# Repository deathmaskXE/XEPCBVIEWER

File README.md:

# XE Delivery

Aplicación web para repartidores independientes: mandados, compras, mensajería, seguimiento público, reputación y rendimiento. Es una sola aplicación multi-repartidor; toda información privada se separa mediante `courierId`, igual al UID de Firebase Authentication.

## Tecnologías

React, Vite, React Router con `HashRouter`, Firebase Authentication y Firestore modular, Chart.js, jsPDF, html2canvas, Leaflet/OpenStreetMap y Lucide. No utiliza Storage, Analytics, Realtime Database, cartera, saldo ni retiros.

## Instalación y ejecución

1. Instala Node.js 20 o superior.
2. Ejecuta `npm install`.
3. Copia `.env.example` como `.env` y completa únicamente las variables públicas de configuración web de Firebase.
4. Ejecuta `npm run dev`.
5. Para validar producción: `npm run build` y `npm run preview`.

La auditoría final del 18 de julio de 2026 confirmó una instalación reproducible y una compilación de producción correcta. El proyecto usa carga diferida por página y `HashRouter`, por lo que no necesita reescrituras de rutas en GitHub Pages.

Si no hay configuración Firebase, la interfaz entra en modo demostración con datos ficticios. También puede activarse de forma explícita con `VITE_DEMO_MODE=true`. Nunca debe activarse en producción.

## Preparar Firebase

1. En un proyecto Firebase existente, activa Authentication por correo/contraseña y Cloud Firestore en modo producción. No actives Analytics ni Storage.
2. Registra una aplicación web y copia sus valores a `.env`; estas claves identifican la app y no sustituyen las reglas de seguridad.
3. Publica reglas e índices con Firebase CLI: `firebase deploy --only firestore`.
4. Crea manualmente el primer usuario administrador en Authentication, copia su UID y crea `users/{uid}` con `uid`, `role: "admin"`, `status: "approved"`, `displayName`, `email`, `phone`, `createdAt` y `updatedAt`. No guardes contraseñas en Firestore.
5. Conserva la cuenta administrativa con autenticación multifactor y acceso restringido a la consola.

## Colecciones

`users`, `couriers`, `courierAccessRoutes`, `licenses`, `clients`, `orders`, `orders/{id}/history`, `ratings`, `complaints`, `auditLogs` y `publicTracking`. Las consultas privadas siempre deben incluir `where('courierId','==',auth.currentUser.uid)`; las reglas vuelven a comprobar la propiedad. `publicTracking` contiene solo una proyección mínima y nunca notas, ganancias, correo, credencial o auditoría.

## Licencias y rutas privadas

La prueba normal usa `type: trial`, `status: trial` y `expiresAt` a 24 horas. La licencia de seis meses usa `type: six_months` y `status: active`. El contador lee el timestamp persistido y nunca lo reinicia localmente. Renovar o cambiar fechas es una operación administrativa auditada.

Una ruta se guarda en `courierAccessRoutes/{token}`. Al regenerarla, una Cloud Function/transacción administrativa debe desactivar la anterior y crear un token criptográficamente aleatorio. La ruta no reemplaza el login: después de autenticar, el UID debe coincidir con `courierId`. No coloque datos sensibles en el token o URL.

## Seguimiento público y confirmación de una hora

El navegador público solo lee `publicTracking/{trackingToken}`. La colección privada `orders` no está abierta al público. Una Cloud Function debe copiar únicamente campos permitidos cada vez que cambia un pedido.

Al entregar, el backend establece `waiting_client_confirmation`, `deliveredAt` y `autoConfirmAt = deliveredAt + 1 hora`. Una función programada completa pedidos vencidos. Una reconciliación en el cliente puede mejorar la experiencia, pero no garantiza ejecución cuando ninguna página está abierta y no debe tener permisos para confirmar arbitrariamente.

## Funciones backend recomendadas (plan Blaze)

- `syncPublicTracking`: proyección segura de pedidos a `publicTracking`.
- `submitPublicConfirmation`, `submitRating` y `submitComplaint`: endpoints con App Check, token de pedido, validación y protección de abuso.
- `autoConfirmDeliveredOrders`: tarea programada para la hora límite.
- `rotateCourierAccessRoute`: invalida la ruta anterior, crea la nueva y audita atómicamente.
- `adminUpdateOrder`, `archiveOrder` y operaciones de licencia: verifican custom claims/rol y registran auditoría.
- Agregados confiables de reputación, estadísticas y consecutivos por repartidor.

Cloud Functions y tareas programadas normalmente requieren el plan Blaze. Los límites y precios deben comprobarse en la documentación vigente de Firebase antes de activarlo.

## GitHub Pages

1. Para este repositorio usa `VITE_BASE_PATH=/XEDELIVERY/` en el entorno de compilación.
2. Ejecuta `npm run build`.
3. Publica con `npm run deploy`; el script usa `gh-pages -d dist`.
4. En GitHub, selecciona la rama `gh-pages` como origen de Pages.

`HashRouter` mantiene estables rutas como `#/acceso/{token}`, `#/seguimiento/{token}`, `#/courier/dashboard` y `#/admin/dashboard` al publicar en una subruta.

## Prueba manual sugerida

Usa `#/seguimiento/demo-128` en modo demo. En Firebase real, crea primero el pedido privado y deja que `syncPublicTracking` produzca su vista pública. Prueba con dos cuentas courier y confirma que cada consulta incluye su UID, y que las reglas rechazan lecturas cruzadas desde el emulador.

Consulta `IMPLEMENTATION_STATUS.md` antes de producción: enumera con precisión lo terminado y lo que necesita backend.

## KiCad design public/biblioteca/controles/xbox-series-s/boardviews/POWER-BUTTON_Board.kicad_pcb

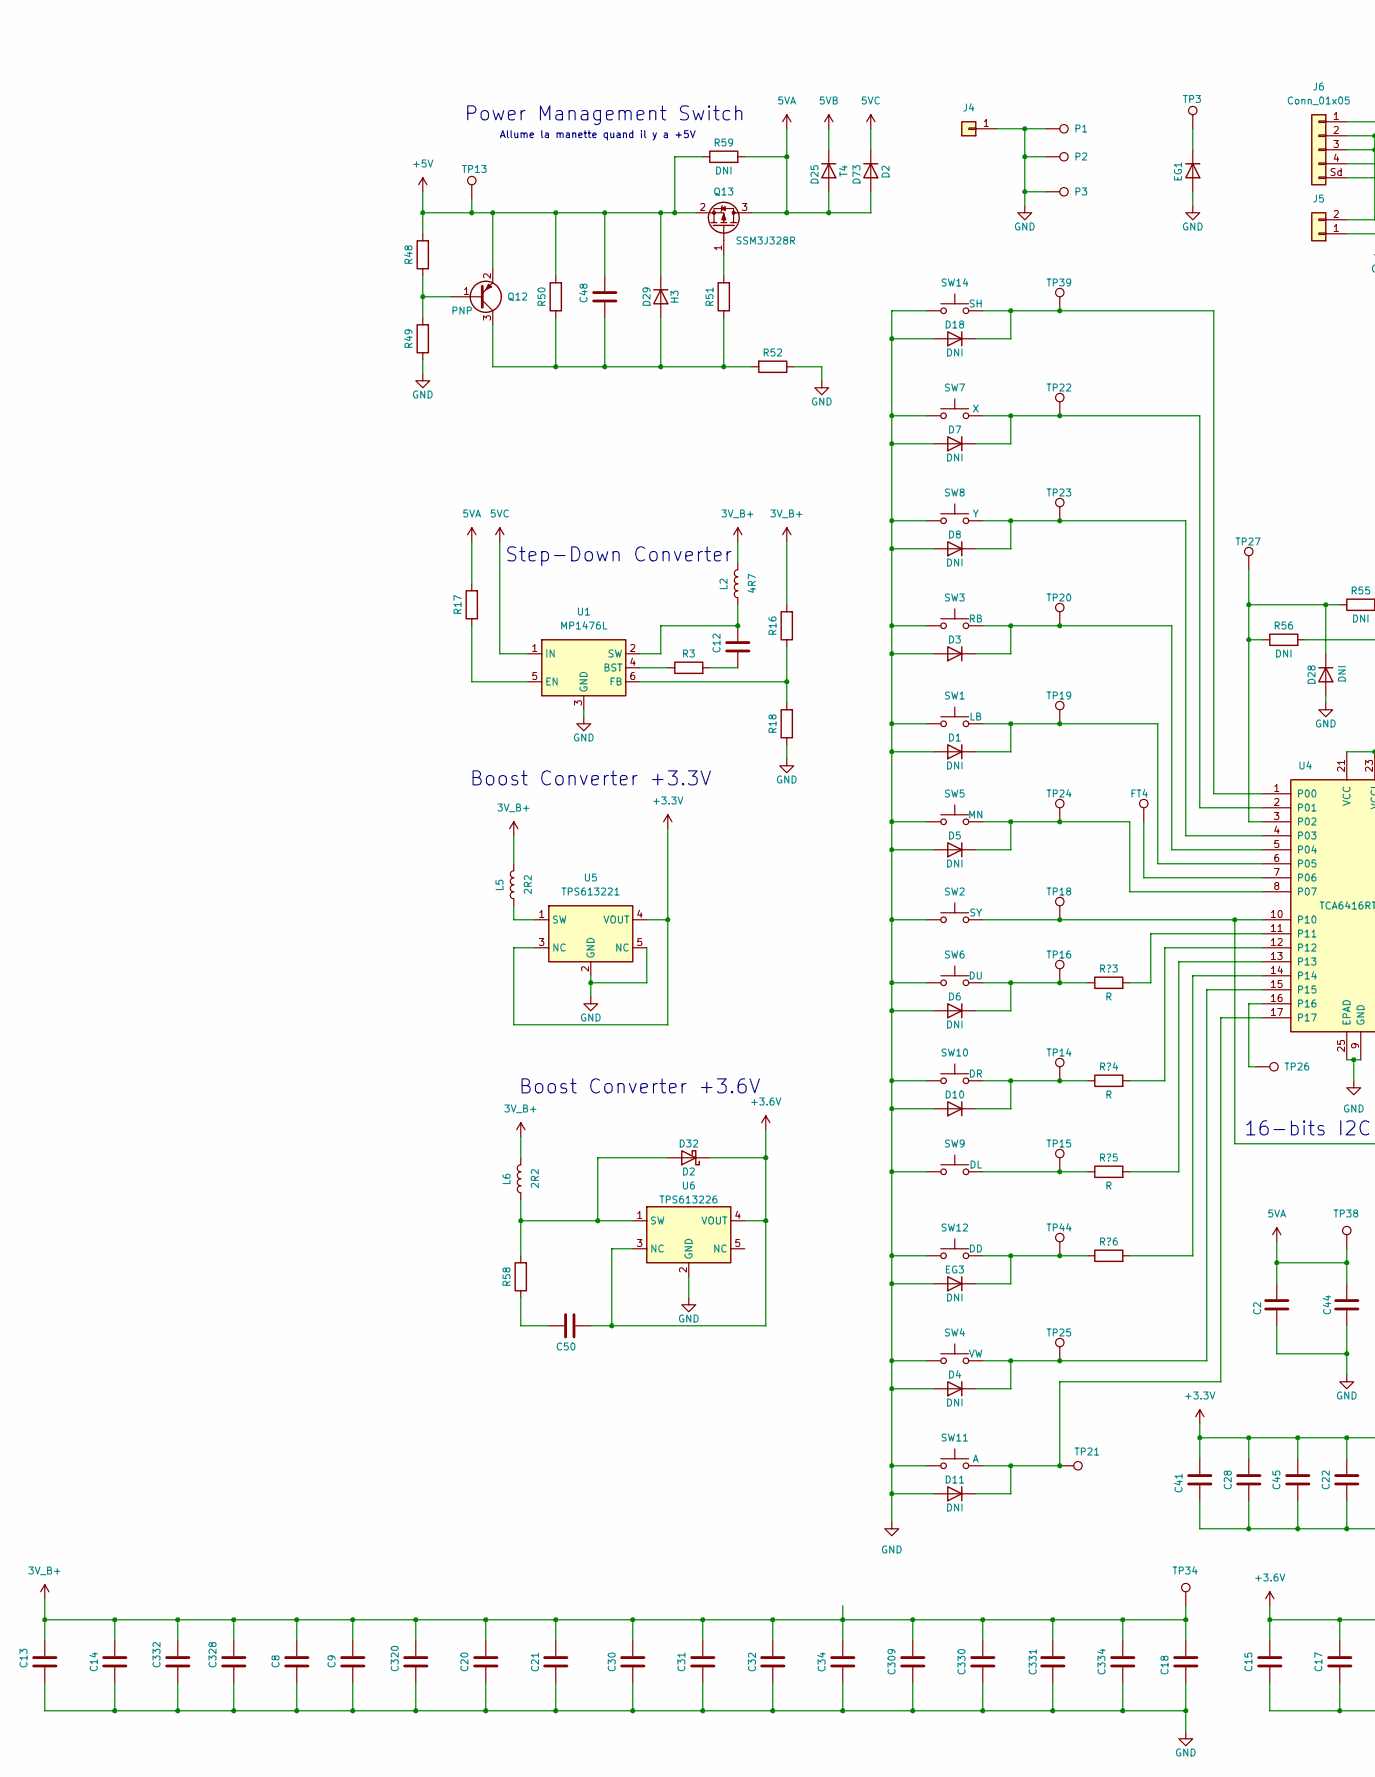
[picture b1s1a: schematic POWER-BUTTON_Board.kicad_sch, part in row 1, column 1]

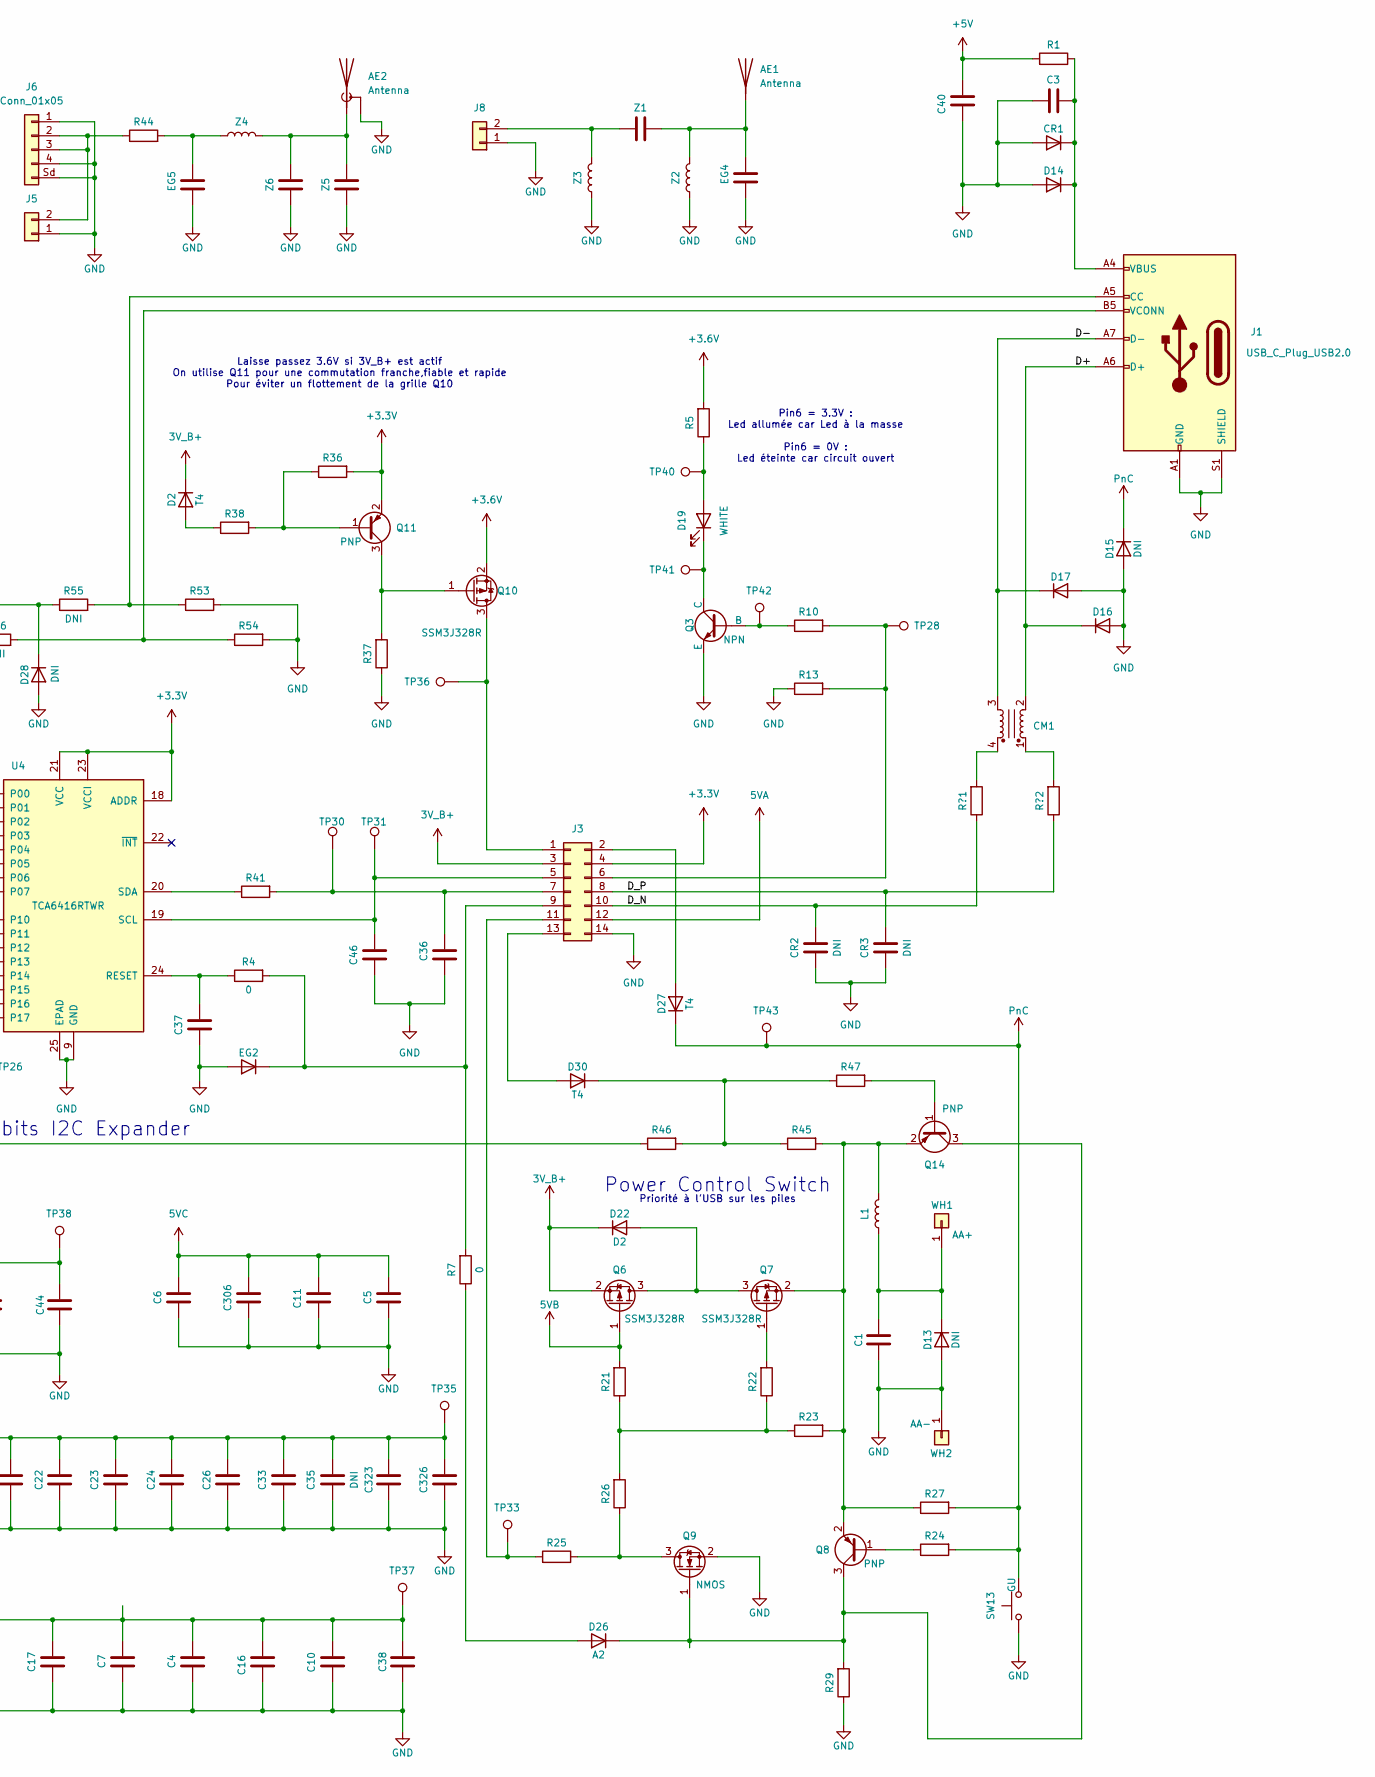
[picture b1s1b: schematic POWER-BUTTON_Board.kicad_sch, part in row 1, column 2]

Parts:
AE1: Antenna; Xbox_RFAntenna2
AE2: Antenna; Xbox_RFAntenna
C1, C12, C14, C15, C28, C36, C37, C45, C46, C48, C50: C; Xbox_C_01005_0402Metric
C2, C4, C8, C9, C13, C16, C20, C23, C26, C30, C31, C32, C34, C306: C; C_0402_1005Metric
C3, C5, C7, C10, C11, C17, C18, C24, C40, C44, C309, C320, C323, C326, C328, C330, C331, C332, C334: C; C_0201_0603Metric
C6: C; C_0504_1310Metric
C21, C22, C41: C; C_01005_0402Metric
C33: C; C_1206_3216Metric
C35: DNI; C_0603_1608Metric
C38: C; C_0603_1608Metric
CM1: Choke_Coilcraft_0603USB-142; L_CommonModeChoke_Coilcraft_0603USB
CR1: D; Xbox_Diode
CR2, CR3: DNI; D_0201_0603Metric
D1, D4, D5, D6, D7, D8, D11, D18: DNI; D_0201_0603Metric
D2, D25, D27, D30: T4; Xbox_Diode
D3, D10: D; D_0201_0603Metric
D13: DNI; R_01005_0402Metric
D14, D16, D17: D; D_01005_0402Metric
D15, D28: DNI; D_01005_0402Metric
D19: WHITE; LED_0805_2012Metric
D22, D32, D73: D2; Xbox_Diode
D26: A2; Xbox_Diode
D29: H3; Xbox_Diode
EG1: D; Xbox_R_01005_0402Metric
EG2: D; D_0201_0603Metric
EG3: DNI; Xbox_R_01005_0402Metric
EG4, EG5: C; C_0402_1005Metric
FT4: TestPoint; Xbox_TestPoint_0.8mm
J1: USB_C_Plug_USB2.0; Xbox_USB_C
J3: Conn_02x07; PinSocket_2x07_P1.27mm_Vertical_SMD
J4: Conn_01x01; Xbox_OtherConnector
J5, J8: Conn_01x02; Xbox_AntennaConnector
J6: Conn_01x05; Xbox_CoaxConnector2
L1: L; L_0402_1005Metric
L2: 4R7; L_APV_ANR4010
L5, L6: 2R2; L_APV_ANR4010
P1, P2, P3: TestPoint; TestPoint_Pad_D2.0mm
Q3: NPN; SOT-23
Q6, Q7, Q10, Q13: SSM3J328R; SOT-23W
Q8, Q11, Q12, Q14: PNP; SOT-523_LongPad
Q9: NMOS; SOT-23
R1, R5, R10, R13, R21, R22, R23, R25, R26, R27, R29, R36, R37, R38, R44, R45, R47, R48, R49, R50, R52, R58: R; R_0402_1005Metric
R3, R16, R18, R53, R54: R; Xbox_R_01005_0402Metric
R4, R7: 0; R_0402_1005Metric
R17, R24, R41: R; R_0201_0603Metric
R46, R51: R; R_01005_0402Metric
R55, R56: DNI; Xbox_R_01005_0402Metric
R59: DNI; R_0402_1005Metric_Pad0.72x0.64mm_HandSolder
R?1, R?2, R?3, R?4, R?5: R; Xbox_R_01005_0402Metric
R?6: Xbox_R_01005_0402Metric
SW1: LB; SW_Tactile_SPST_Angled_PTS645Vx39-2LFS
SW2: SY; Xbox_VerticalSwitch
SW3: RB; SW_Tactile_SPST_Angled_PTS645Vx39-2LFS
SW4: VW; Xbox_SwitchContactPad
SW5: MN; Xbox_SwitchContactPad
SW6: DU; Xbox_SwitchContactPad2
SW7: X; Xbox_SwitchContactPad
SW8: Y; Xbox_SwitchContactPad
SW9: DL; Xbox_SwitchContactPad2
SW10: DR; Xbox_SwitchContactPad2
SW11: A; Xbox_SwitchContactPad
SW12: DD; Xbox_SwitchContactPad2
SW13: GU; Xbox_XboxButton
SW14: SH; Xbox_SwitchContactPad
TP3: TestPoint; TestPoint_Pad_2.5x2.5mm
TP13, TP14, TP15, TP16, TP18, TP19, TP20, TP21, TP22, TP23, TP24, TP25, TP26, TP27, TP28, TP30, TP31, TP33, TP34, TP35, TP36, TP37, TP38, TP39, TP40, TP41, TP42, TP43, TP44: TestPoint; Xbox_TestPoint_0.8mm
U1: MP1476L; SOT-563
U4: TCA6416RTWR; WQFN-24-1EP_4x4mm_P0.5mm_EP2.45x2.45mm
U5: TPS613221; SOT-23-5
U6: TPS613226; SOT-23-5
WH1: AA+; Xbox_BatteryHolder1
WH2: AA-; Xbox_BatteryHolder2
Z1: C; L_0402_1005Metric
Z2, Z3, Z4: L; L_0402_1005Metric
Z5, Z6: C; C_0402_1005Metric

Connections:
3V_B+: C8.2, C9.2, C13.2, C14.2, C18.2, C20.2, C21.2, C30.2, C31.2, C32.2, C34.2, C309.2, C320.2, C328.2, C330.2, C331.2, C332.2, C334.2, D2.1 (K), D22.1 (K), J3.3, L2.2, L5.2, L6.2, Q6.2 (S), R16.2, TP34.1
5VA: C2.2, C44.2, D25.2 (A), D73.2 (A), J3.12, Q13.3 (D), R17.2, R59.2, TP38.1
5VB: D25.1 (K), Q6.1 (G), R21.2
5VC: C5.2, C6.2, C11.2, C306.2, D73.1 (K), U1.1 (IN)
+3.3V: C22.2, C23.2, C24.2, C26.2, C28.2, C33.2, C35.2, C41.2, C45.2, C323.2, C326.2, J3.4, Q11.2 (E), R36.2, TP35.1, U4.18 (ADDR), U4.21 (VCC), U4.23 (VCCI), U5.3 (NC), U5.4 (VOUT)
+3.6V: C4.2, C7.2, C10.2, C15.2, C16.2, C17.2, C38.2, C50.1, D32.1 (K), Q10.2 (S), R5.2, TP37.1, U6.3 (NC), U6.4 (VOUT)
+5V: C40.1, C48.2, D29.1 (K), Q12.2 (E), Q13.2 (S), R1.2, R48.2, R50.2, R59.1, TP13.1
/D+: CM1.2, D16.1 (K), J1.A6 (D+)
/D-: CM1.3, D17.1 (K), J1.A7 (D-)
/D_N: CR2.2, J3.10, R?1.1
/D_P: CR3.2, J3.8, R?2.1
GND: AE2.2 (Shield), C1.1, C2.1, C3.2, C4.1, C5.1, C6.1, C7.1, C8.1, C9.1, C10.1, C11.1, C13.1, C14.1, C15.1, C16.1, C17.1, C18.1, C20.1, C21.1, C22.1, C23.1, C24.1, C26.1, C28.1, C30.1, C31.1, C32.1, C33.1, C34.1, C35.1, C36.1, C37.1, C38.1, C40.2, C41.1, C44.1, C45.1, C46.1, C306.1, C309.1, C320.1, C323.1, C326.1, C328.1, C330.1, C331.1, C332.1, C334.1, CR1.2 (A), CR2.1, CR3.1, D1.2 (A), D3.2 (A), D4.2 (A), D5.2 (A), D6.2 (A), D7.2 (A), D8.2 (A), D10.2 (A), D11.2 (A), D13.2 (A), D14.2 (A), D15.2 (A), D16.2 (A), D17.2 (A), D18.2 (A), D28.2 (A), EG1.2 (A), EG2.2 (A), EG3.2 (A), EG4.1, EG5.1, J1.A1 (GND), J1.A12 (GND), J1.B1 (GND), J1.B12 (GND), J1.S1 (SHIELD), J3.14, J4.1, J5.1, J6.1, J6.4, J6.Sd (Pin_5), J8.1, P1.1, P2.1, P3.1, Q3.2 (E), Q9.2 (S), R13.1, R18.1, R29.1, R37.1, R49.1, R52.1, R53.2, R54.2, SW1.1, SW2.1, SW3.1, SW4.1, SW5.1, SW6.1, SW7.1, SW8.1, SW9.1, SW10.1, SW11.1, SW12.1, SW13.1, SW14.1, U1.3 (GND), U4.9 (GND), U4.25 (EPAD), U5.2 (GND), U5.5 (NC), U6.2 (GND), WH2.1, Z2.1, Z3.1, Z5.1, Z6.1
unnamed: AE1.1 (A), EG4.2, Z1.1, Z2.2
unnamed: AE2.1 (A), Z4.2, Z5.2, Z6.2
unnamed: C12.1, R3.2
unnamed: C50.2, R58.1
unnamed: CM1.1, R?2.2
unnamed: CM1.4, R?1.2
unnamed: C3.1, CR1.1 (K), D14.1 (K), J1.A4 (VBUS), J1.A9 (VBUS), J1.B4 (VBUS), J1.B9 (VBUS), R1.1
unnamed: D1.1 (K), SW1.2, TP19.1, U4.6 (P05)
unnamed: D2.2 (A), R38.1
unnamed: D3.1 (K), SW3.2, TP20.1, U4.5 (P04)
unnamed: D4.1 (K), SW4.2, TP25.1, U4.15
unnamed: D5.1 (K), SW5.2, TP24.1, U4.8 (P07)
unnamed: D6.1 (K), R?3.1, SW6.2, TP16.1
unnamed: D7.1 (K), SW7.2, TP22.1, U4.2 (P01)
unnamed: D8.1 (K), SW8.2, TP23.1, U4.4 (P03)
unnamed: D10.1 (K), R?4.1, SW10.2, TP14.1
unnamed: D11.1 (K), SW11.2, TP21.1, U4.17
unnamed: C1.2, D13.1 (K), L1.1, WH1.1
unnamed: D18.1 (K), SW14.2, TP39.1, U4.1 (P00)
unnamed: D19.2 (A), R5.1, TP40.1
unnamed: D19.1 (K), Q3.3 (C), TP41.1
unnamed: D22.2 (A), Q6.3 (D), Q7.3 (D)
unnamed: D26.2 (A), R7.1
unnamed: D26.1 (K), Q8.3 (C), Q9.1 (G), Q14.3 (C), R29.2
unnamed: D27.2 (A), J3.2
unnamed: D28.1 (K), R55.1, R56.1, TP27.1, U4.3 (P02)
unnamed: C48.1, D29.2 (A), Q12.3 (C), R50.1, R51.1, R52.2
unnamed: D30.2 (A), J3.13
unnamed: D30.1 (K), R45.1, R46.2, R47.1
unnamed: D32.2 (A), L6.1, R58.2, U6.1 (SW)
unnamed: EG1.1 (K), TP3.1
unnamed: EG2.1 (K), J3.9, R4.2, R7.2
unnamed: EG3.1 (K), R?6.1, SW12.2, TP44.1
unnamed: EG5.2, R44.2, Z4.1
unnamed: J1.A5 (CC), R53.1, R55.2
unnamed: J1.B5 (VCONN), R54.1, R56.2
unnamed: J3.1, Q10.3 (D), TP36.1
unnamed: C46.2, J3.5, TP31.1, U4.19 (SCL)
unnamed: J3.6, R10.2, R13.2, TP28.1
unnamed: C36.2, J3.7, R41.2, TP30.1
unnamed: J3.11, R25.2, TP33.1
unnamed: J5.2, J6.2, J6.3, R44.1
unnamed: J8.2, Z1.2, Z3.2
unnamed: Q3.1 (B), R10.1, TP42.1
unnamed: Q7.1 (G), R22.2
unnamed: Q8.1 (B), R24.1
unnamed: Q9.3 (D), R25.1, R26.1
unnamed: Q10.1 (G), Q11.3 (C), R37.2
unnamed: Q11.1 (B), R36.1, R38.2
unnamed: Q12.1 (B), R48.1, R49.2
unnamed: Q13.1 (G), R51.2
unnamed: Q14.1 (B), R47.2
unnamed: L1.2, Q7.2 (S), Q8.2 (E), Q14.2 (E), R23.2, R27.1, R45.2
unnamed: R21.1, R22.1, R23.1, R26.2
unnamed: R?5.1, SW9.2, TP15.1
unnamed: R3.1, U1.4 (BST)
unnamed: R17.1, U1.5 (EN)
unnamed: R16.1, R18.2, U1.6 (FB)
unnamed: C12.2, L2.1, U1.2 (SW)
unnamed: FT4.1, U4.7 (P06)
unnamed: R46.1, SW2.2, TP18.1, U4.10
unnamed: R?3.2, U4.11
unnamed: R?4.2, U4.12
unnamed: R?5.2, U4.13
unnamed: R?6.2, U4.14
unnamed: TP26.1, U4.16
unnamed: C37.2, R4.1, U4.24 (RESET)
unnamed: R41.1, U4.20 (SDA)
unnamed: L5.1, U5.1 (SW)
PnC: D15.1 (K), D27.1 (K), R24.2, R27.2, SW13.2, TP43.1

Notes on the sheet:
Priorité à l'USB sur les piles
Boost Converter +3.3V
16-bits I2C Expander
Step-Down Converter
Boost Converter +3.6V
Pin6 = 3.3V : Led allumée car Led à la masse Pin6 = 0V : Led éteinte car circuit ouvert
Power Management Switch
Power Control Switch
Laisse passez 3.6V si 3V_B+ est actif On utilise Q11 pour une commutation franche,fiable et rapide Pour éviter un flottement de la grille Q10
Allume la manette quand il y a +5V

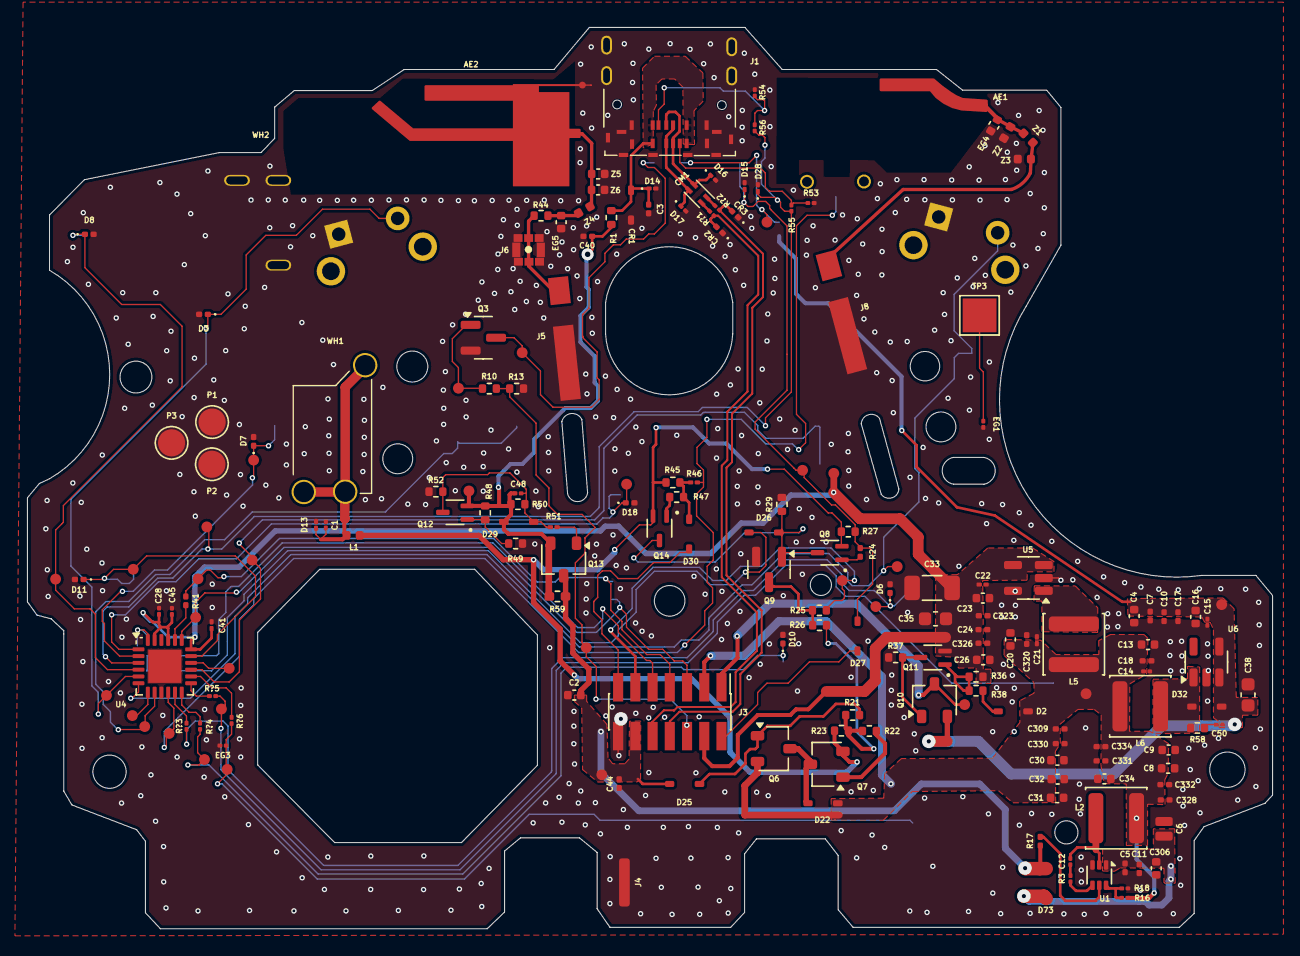
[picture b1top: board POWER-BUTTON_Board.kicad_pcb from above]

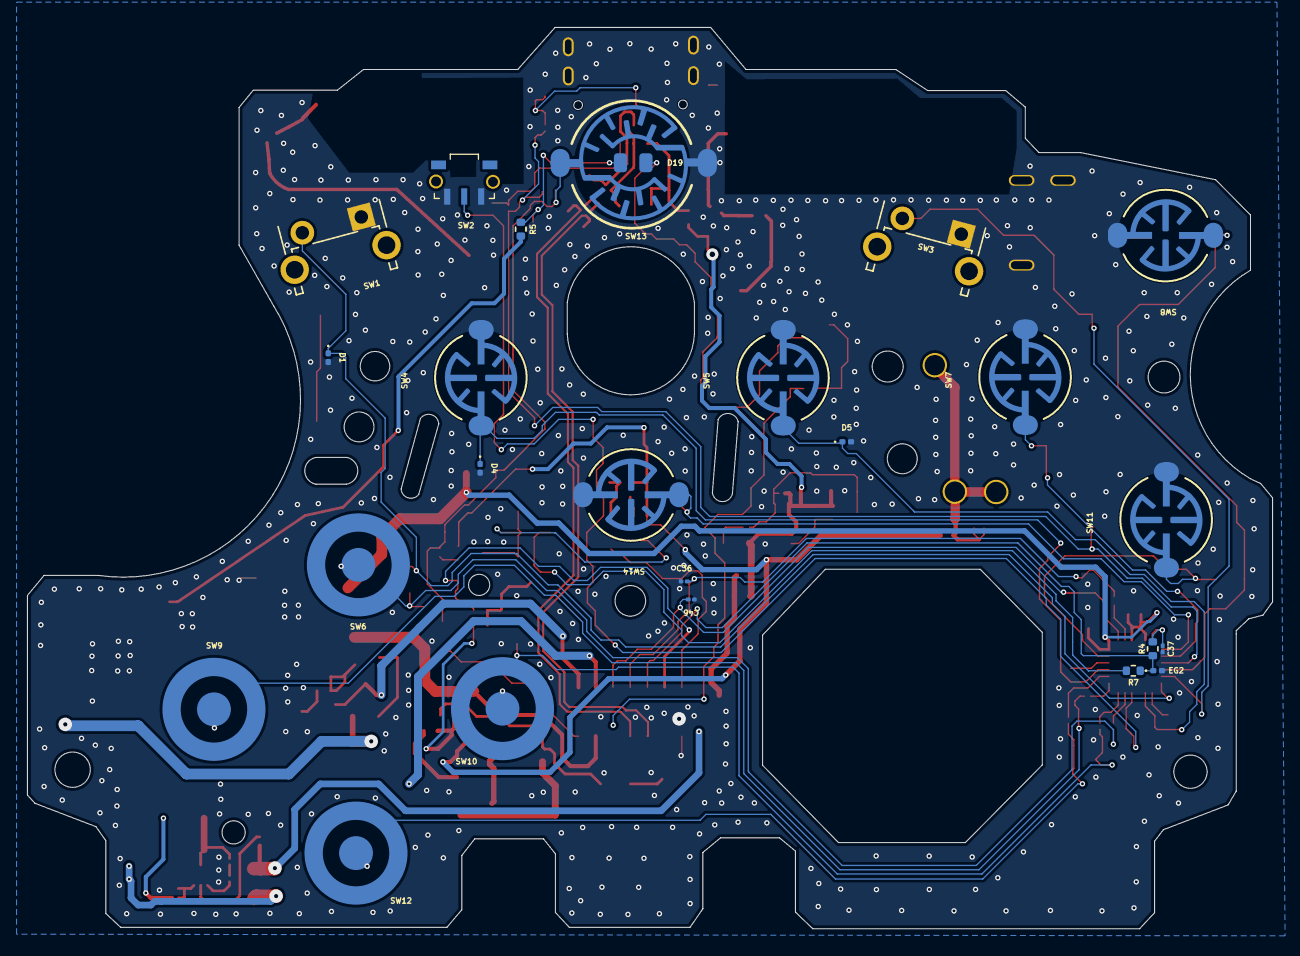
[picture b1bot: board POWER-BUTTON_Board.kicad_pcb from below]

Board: 4 copper layers, 91.8 x 66.4 mm, 211 parts (25 on the bottom side), 82 nets.

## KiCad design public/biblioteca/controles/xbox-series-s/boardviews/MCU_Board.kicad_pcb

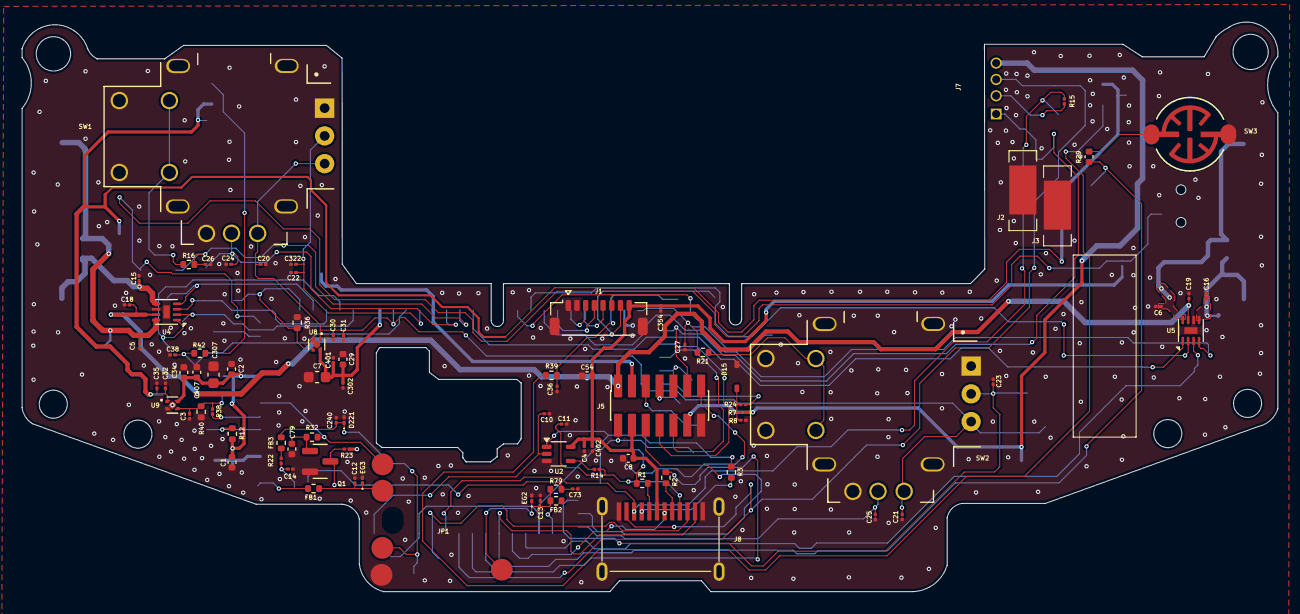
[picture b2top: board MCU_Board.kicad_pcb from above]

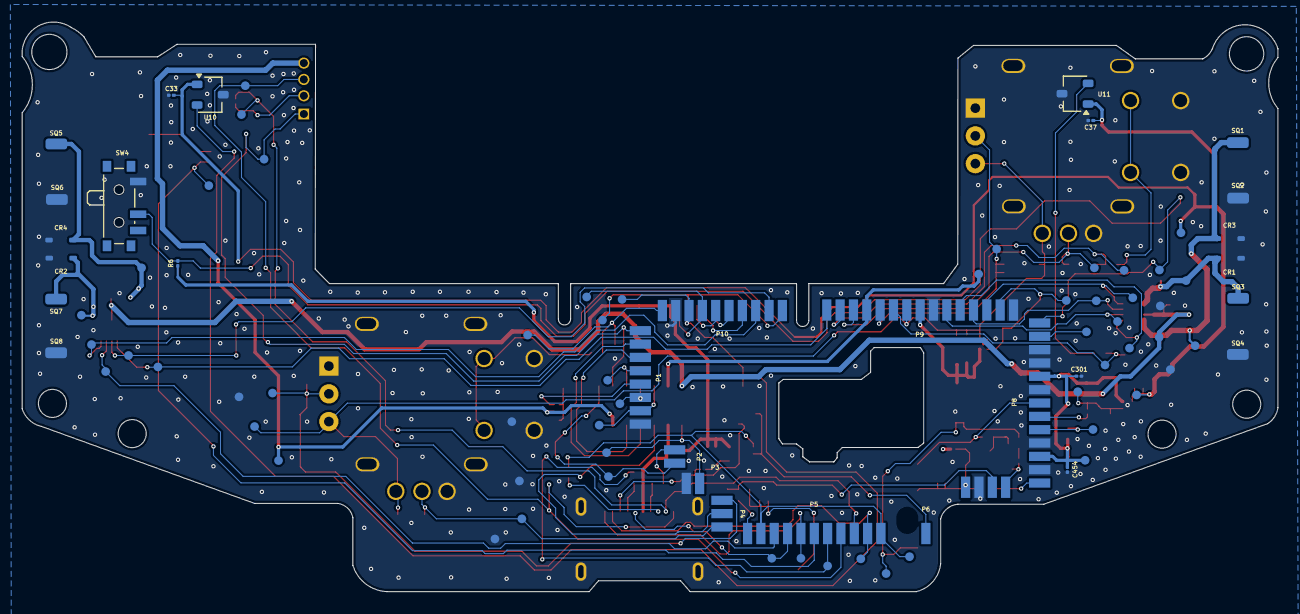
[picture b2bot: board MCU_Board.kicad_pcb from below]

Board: 4 copper layers, 115.3 x 52.3 mm, 173 parts (75 on the bottom side), 81 nets.

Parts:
C1, C2, C8, C29, C34, C54, C79, C407: C; C_0402_1005Metric
C3, C4, C10, C11, C12, C13, C18, C19, C20, C21, C22, C23, C24, C25, C26, C27, C30, C31, C32, C33, C35, C36, C37, C38, C73, C240, C301, C302, C322, C354, C401, C402, C454: C; Xbox_C_01005_0402Metric
C5, C6, C14, C15, C16: DNI; Xbox_C_01005_0402Metric
C7, C307: C; C_0603_1608Metric
CR1, CR2, CR3, CR4: D; Xbox_Diode
D15: D; Xbox_Diode
D221: D; D_01005_0402Metric
EG2, EG3: D; D_01005_0402Metric
FB1, FB2, FB3: FerriteBead; R_0402_1005Metric
FT1, FT2: TestPoint; Xbox_TestPoint_0.8mm
J1: Conn_01x08; Xbox_DebugConnector
J2, J3: Conn_01x01; Xbox_WireConnector
J5: Conn_02x07; PinSocket_2x07_P1.27mm_Vertical_SMD
J7: Conn_01x04; Xbox_EdgeConnector
J8: External Connector; Xbox_ExpansionPort
JP1: Conn_01x05; Xbox_Jack
P1: 1-8; Xbox_SOC_to_MCU_1_8
P2: 9-10; Xbox_SOC_to_MCU_9_10
P3: 11-12; Xbox_SOC_to_MCU_11_12
P4: 13-15; Xbox_SOC_to_MCU_13_15
P5: 16-26; Xbox_SOC_to_MCU_16_26
P6: 27; Xbox_SOC_to_MCU_27
P7: 28-31; Xbox_SOC_to_MCU_28_31
P8: 32_44; Xbox_SOC_to_MCU_32_44
P9: 59-45; Xbox_SOC_to_MCU_45_59
P10: 69-60; Xbox_SOC_to_MCU_60_69
Q1: BSS138; SOT-23
R1, R2, R3, R16, R21: 33; R_0402_1005Metric
R6, R23: 10k; Xbox_R_01005_0402Metric
R7, R8: 100k; Xbox_R_01005_0402Metric
R12: DNI; R_0402_1005Metric
R14, R15, R22, R38: 0; Xbox_R_01005_0402Metric
R24: 1.5k; Xbox_R_01005_0402Metric
R29: 100; C_0402_1005Metric
R32: 0; R_0402_1005Metric
R36, R40: 100k; R_0402_1005Metric
R39, R42: 100; R_0402_1005Metric
R79: 1k; R_0402_1005Metric
SQ1, SQ2, SQ3, SQ4, SQ5, SQ6, SQ7, SQ8: Conn_01x01; SolderWirePad_1x01_SMD_1x2mm
SW1, SW2: Joystick; Xbox_Joystick
SW3: SW_Push; Xbox_SwitchContactPad
SW4: DNI; SW_SPDT_PCM12
TP3, TP4, TP5, TP7, TP9, TP11, TP14, TP16, TP21, TP22, TP24, TP26, TP27, TP28, TP29, TP30, TP31, TP32, TP33, TP34, TP35, TP36, TP41, TP42, TP43, TP49, TP50, TP54, TP63, TP64, TP65, TP67, TP68, TP69, TP71, TP72, TP103, TP104, TP105, TP106, TP107, TP108, TP109, TP110, TP111, TP112, TP113, TP114, TP115, TP116, TP117, TP118, TP119: TestPoint; Xbox_TestPoint_0.8mm
U2: SN74LVC1G125DCK; Texas_R-PDSO-G5_DCK-5
U4, U5: DFN-8-1EP_2x2mm_P0.5mm_EP0.6x1.2mm
U8: TLV70718; Texas_X2SON-4_1x1mm_P0.65mm
U9: TLV70732; Texas_X2SON-4_1x1mm_P0.65mm
U10, U11: A1304; SOT-23W

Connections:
3V_B+: J5.3, P9.12, TP11.1
+1V8: C20.2, C21.2, C30.2, C31.2, P9.9, SW1.H1 (H+), SW1.V3 (V-), SW2.H1 (H+), SW2.V3 (V-), TP103.1, U8.1 (OUT)
+3.3V: C1.2, C2.2, C4.2, C7.2, C8.2, C29.2, C34.2, C54.2, C301.2, C302.2, C307.2, C354.2, C401.2, C402.2, C407.2, C454.2, J1.8, J5.4, J8.6, P8.3, P8.9, P9.8, R6.1, R12.1, R23.1, TP9.1, U2.5 (VCC), U8.4 (IN), U9.4 (IN)
+3.6V: C18.2, C19.2, J5.1, TP7.1, U4.7 (VBB), U5.7 (VBB)
/1: J5.11, J7.1, P1.1, TP14.1
/2: J5.8, P1.2
/3: J5.10, P1.3
/4: J5.9, P1.4, TP35.1
/5: P1.5, R24.1
/6: J5.7, P1.6, TP33.1
/7: J5.5, P1.7, TP34.1
/9: P2.1, R1.1
/10: J5.13, P2.2, TP119.1
/12: J5.2, P3.2, TP16.1
/13: C23.2, P4.1, SW2.H2 (H), TP65.1
/14: J5.6, P4.2
/15: C25.1, P4.3, SW2.V2 (V), TP112.1
/16: FB2.1, P5.1
/17: P5.2, P5.11, R3.1, TP114.1, U2.1
/18: P5.3, TP111.1, U5.3 (LIN2)
/19: J8.7, P5.4, TP115.1
/20: J8.11, P5.5, TP118.1
/21: P5.6, R29.1, TP41.1
/22: P5.7, R2.1, TP116.1
/25: J8.10, P5.10, TP117.1
/27: C10.2, P6.1, U2.2
/28: P7.1, Q1.3 (D), R23.2
/30: C73.2, P7.3, R79.2
/31: C14.2, P7.4, R22.2
/32: FB1.1, P8.1
/36: P8.5, R12.2, TP4.1
/37: P8.6, R38.2
/38: JP1.PK3 (Pin_1), P8.7, R32.1
/43: P8.12, TP3.1
/44: P8.13, R6.2, SW4.2 (B), TP69.1
/46: P9.2, R36.2, TP36.1, U8.3 (EN)
/47: P9.3, TP105.1, U4.4 (HIN2)
/48: P9.4, TP107.1, U4.3 (LIN2)
/49: P9.5, TP104.1, U4.1 (HIN1)
/50: P9.6, TP106.1, U4.2 (LIN1)
/54: C38.2, P9.10, R42.2, TP68.1
/55: C22.2, C322.2, P9.11, SW1.H2 (H), TP63.1
/57: C24.2, P9.13, SW1.V2 (V), TP64.1
/58: C26.2, P9.14, R16.2, TP42.1
/59: P9.15, TP108.1, U5.1 (HIN1)
/60: J1.6, P10.1, TP71.1
/61: P10.2, TP110.1, U5.2 (LIN1)
/62: P10.3, TP109.1, U5.4 (HIN2)
/63: J1.4, P10.4
/64: J1.3, P10.5
/65: J1.5, P10.6
/66: J1.7, P10.7, TP72.1
/67: C36.2, P10.8, R39.2, TP67.1
/69: C27.2, P10.10, R21.1, TP43.1
GND: C1.1, C2.1, C3.1, C4.1, C5.1, C6.1, C7.1, C8.1, C10.1, C11.2, C12.1, C13.1, C14.1, C15.1, C16.1, C18.1, C19.1, C20.1, C21.1, C22.1, C23.1, C24.1, C25.2, C26.1, C27.1, C29.1, C30.1, C31.1, C32.1, C33.1, C34.1, C35.1, C36.1, C37.1, C38.1, C54.1, C73.1, C79.2, C240.1, C301.1, C302.1, C307.1, C322.1, C354.1, C401.1, C402.1, C407.1, C454.1, CR1.2 (A), CR2.2 (A), CR3.2 (A), CR4.2 (A), D15.2 (A), D221.2 (A), EG2.2 (A), EG3.2 (A), FT1.1, FT2.1, J1.1, J1.2, J2.1, J3.1, J5.14, J8.1, J8.12, JP1.PK1 (Pin_3), P1.8, P3.1, P7.2, P8.2, P8.4, P8.8, P8.10, P8.11, P9.1, P9.7, P10.9, Q1.2 (S), R8.2, R36.1, R40.1, SQ2.1, SQ4.1, SQ6.1, SQ8.1, SW1.B1A (SEL+), SW1.B1B (SEL+), SW1.H3 (H-), SW1.S1 (SHIELD), SW1.S2 (SHIELD), SW1.S3 (SHIELD), SW1.S4 (SHIELD), SW1.V1 (V+), SW2.B1A (SEL+), SW2.B1B (SEL+), SW2.H3 (H-), SW2.S1 (SHIELD), SW2.S2 (SHIELD), SW2.S3 (SHIELD), SW2.S4 (SHIELD), SW2.V1 (V+), SW3.1, SW4.1 (C), TP21.1, TP22.1, TP24.1, TP26.1, U2.3 (GND), U4.6 (GND), U4.9 (EP), U5.6 (GND), U5.9 (EP), U8.2 (GND), U8.5 (Pad), U9.2 (GND), U9.5 (Pad), U10.3 (GND), U11.3 (GND)
Heavy_Motor: C15.2, CR1.1 (K), SQ3.1, TP28.1, U4.5 (OUT2)
LT_Motor: C5.2, CR3.1 (K), SQ1.1, TP27.1, U4.8 (OUT1)
Light_Motor: C16.2, CR2.1 (K), SQ7.1, TP30.1, U5.5 (OUT2)
unnamed: D15.1 (K), R7.2, R8.1, R24.2
unnamed: C240.2, D221.1 (K), FB3.2, JP1.PK6 (Pin_4), TP54.1
unnamed: C13.2, EG2.1 (K), FB2.2, JP1.PK4 (Pin-5), R79.1
unnamed: C12.2, EG3.1 (K), FB1.2, JP1.PK2 (Pin_2)
unnamed: FB3.1, R22.1
unnamed: J7.2, R15.2
unnamed: J8.4, R3.2
unnamed: J8.5, R1.2
unnamed: J8.8, R2.2
unnamed: C11.1, J8.9, R14.2
unnamed: C79.1, Q1.1 (G), R32.2
unnamed: R14.1, U2.4
unnamed: R16.1, SW1.B2A (SEL-), SW1.B2B (SEL-)
unnamed: R21.2, SW2.B2A (SEL-), SW2.B2B (SEL-)
unnamed: R29.2, SW3.2
unnamed: C3.2, R38.1, R40.2, TP113.1, U9.3 (EN)
unnamed: R39.1, U10.2 (VOUT)
unnamed: R42.1, U11.2 (VOUT)
RT_Motor: C6.2, CR4.1 (K), SQ5.1, TP29.1, U5.8 (OUT1)
SCL2: J8.3, P5.9, R15.1, TP32.1
SDA2: J7.3, J8.2, P5.8, TP31.1
TRG+: C32.2, C33.2, C35.2, C37.2, TP49.1, TP50.1, U9.1 (OUT), U10.1 (VCC), U11.1 (VCC)
VBUS: J5.12, J7.4, R7.1, TP5.1
